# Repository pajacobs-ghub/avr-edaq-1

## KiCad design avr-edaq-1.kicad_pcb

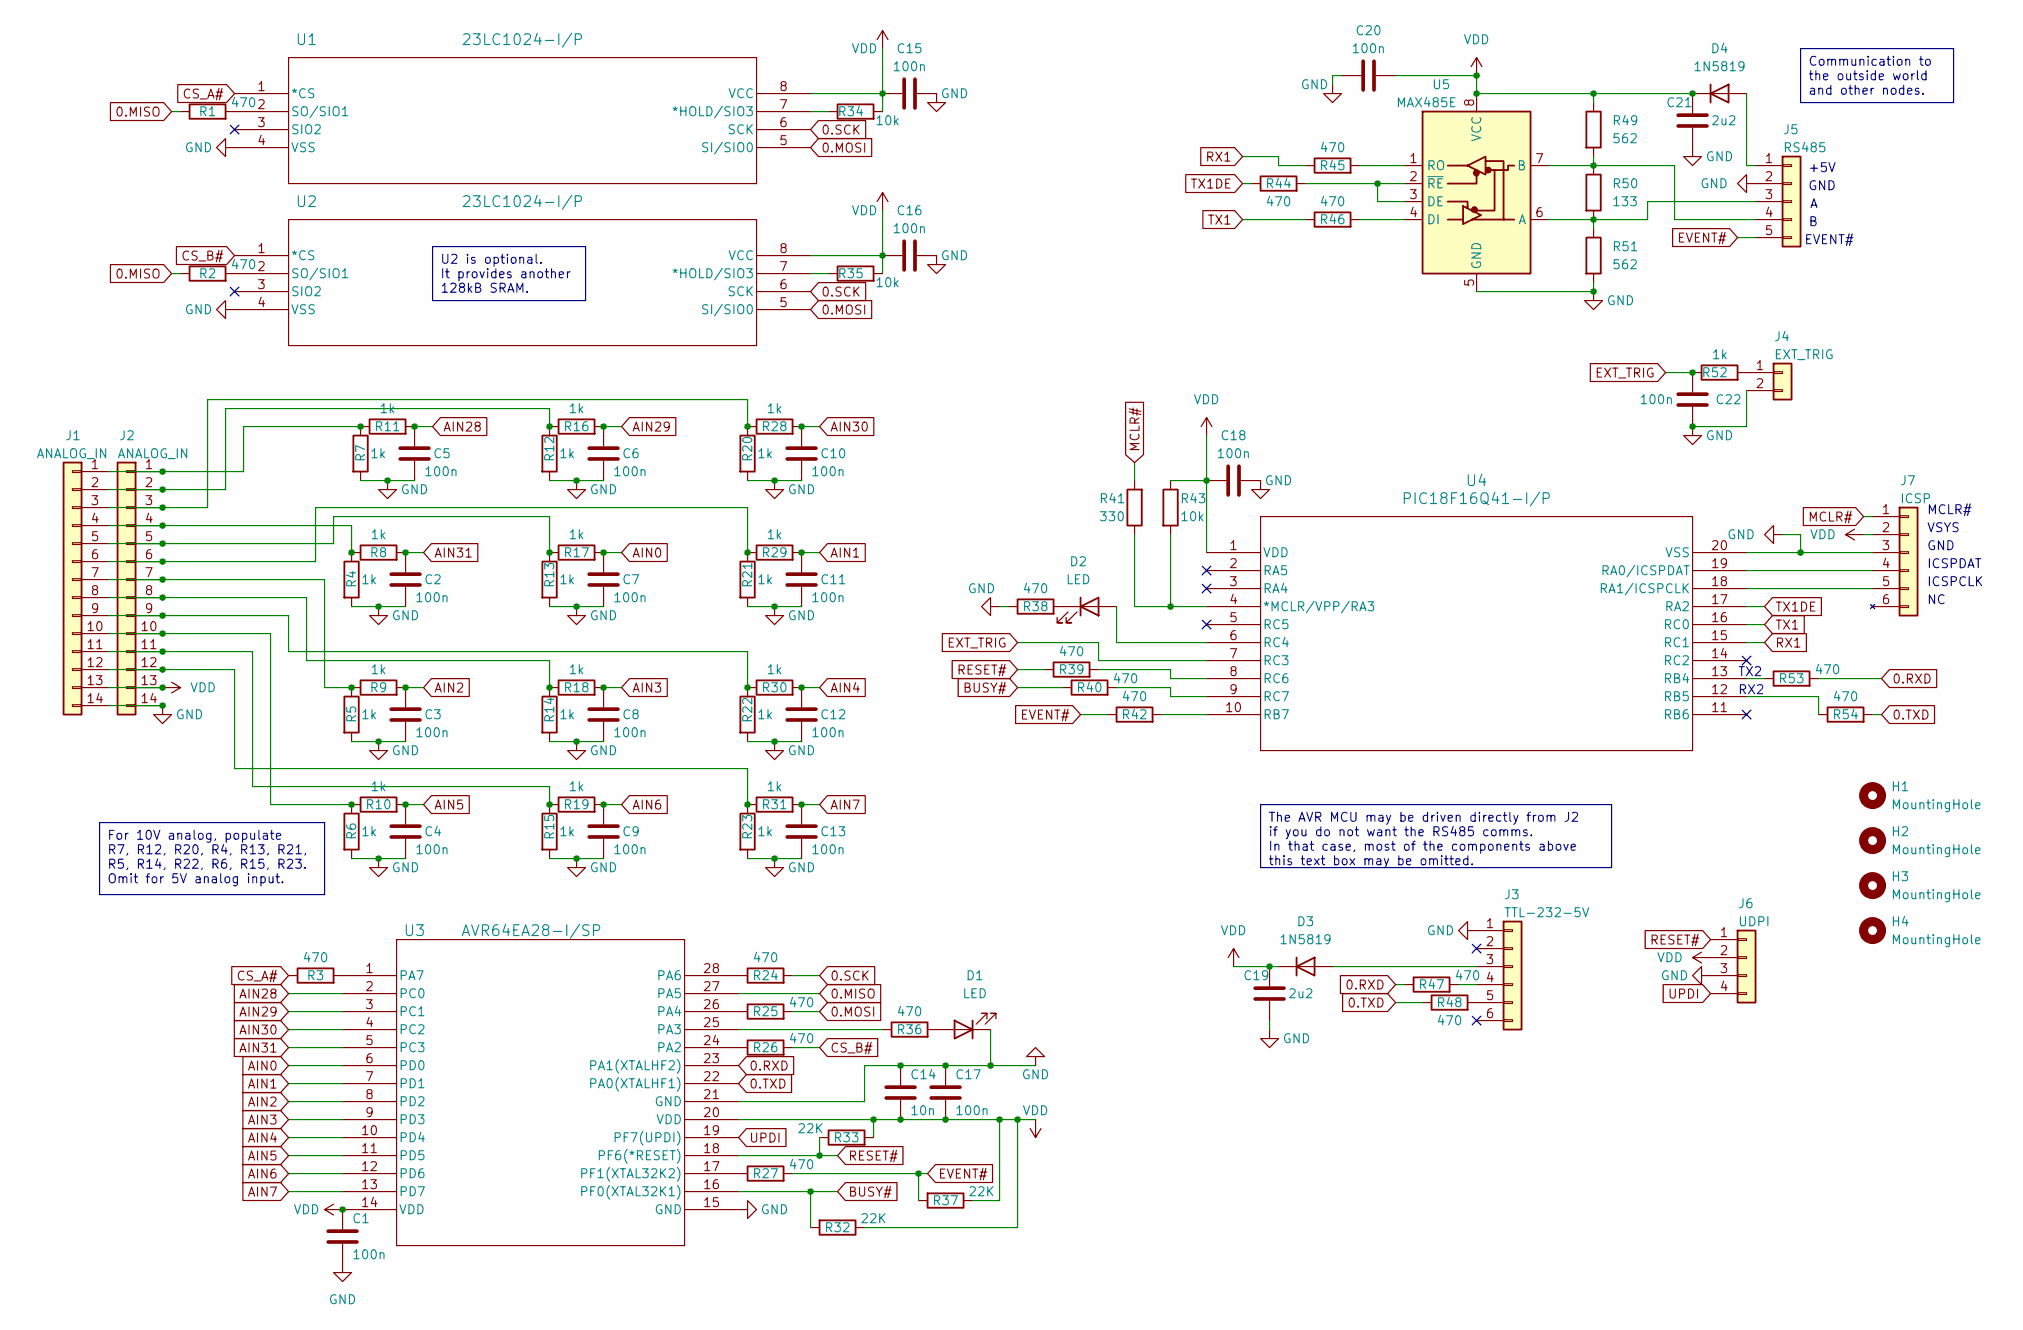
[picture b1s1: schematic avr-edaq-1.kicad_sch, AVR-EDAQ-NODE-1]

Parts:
C1, C2, C3, C4, C5, C6, C7, C8, C9, C10, C11, C12, C13, C15, C16, C17, C18, C20, C22: 100n; C_Disc_D4.7mm_W2.5mm_P5.00mm
C14: 10n; C_Disc_D4.7mm_W2.5mm_P5.00mm
C19, C21: 2u2; C_Disc_D4.7mm_W2.5mm_P5.00mm
D1, D2: LED; LED_D3.0mm
D3, D4: 1N5819; D_DO-41_SOD81_P10.16mm_Horizontal
H1, H2, H3, H4: MountingHole; MountingHole_3.2mm_M3
J1, J2: ANALOG_IN; PinHeader_1x14_P2.54mm_Vertical
J3: TTL-232-5V; PinHeader_1x06_P2.54mm_Vertical
J4: EXT_TRIG; PinHeader_1x02_P2.54mm_Vertical
J5: RS485; PinHeader_1x05_P2.54mm_Vertical
J6: UDPI; PinHeader_1x04_P2.54mm_Vertical
J7: ICSP; PinHeader_1x06_P2.54mm_Vertical
R1, R2, R3, R24, R25, R26, R27, R36, R38, R39, R40, R42, R44, R45, R46, R47, R48, R53, R54: 470; R_Axial_DIN0207_L6.3mm_D2.5mm_P10.16mm_Horizontal
R4, R5, R6, R7, R8, R9, R10, R11, R12, R13, R14, R15, R16, R17, R18, R19, R20, R21, R22, R23, R28, R29, R30, R31, R52: 1k; R_Axial_DIN0207_L6.3mm_D2.5mm_P10.16mm_Horizontal
R32, R33, R37: 22K; R_Axial_DIN0207_L6.3mm_D2.5mm_P10.16mm_Horizontal
R34, R35, R43: 10k; R_Axial_DIN0207_L6.3mm_D2.5mm_P10.16mm_Horizontal
R41: 330; R_Axial_DIN0207_L6.3mm_D2.5mm_P10.16mm_Horizontal
R49, R51: 562; R_Axial_DIN0207_L6.3mm_D2.5mm_P10.16mm_Horizontal
R50: 133; R_Axial_DIN0207_L6.3mm_D2.5mm_P10.16mm_Horizontal
U1, U2: 23LC1024-I/P; DIP-8_W7.62mm
U3: AVR64EA28-I/SP; DIP-28_W7.62mm
U4: PIC18F16Q41-I/P; DIP-20_W7.62mm
U5: MAX485E; DIP-8_W7.62mm

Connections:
0.MISO: R1.1, R2.1, U3.27 (PA5)
0.MOSI: R25.2, U1.5 (SI/SIO0), U2.5 (SI/SIO0)
0.RXD: R47.1, R53.2, U3.23 (PA1(XTALHF2))
0.SCK: R24.2, U1.6 (SCK), U2.6 (SCK)
0.TXD: R48.1, R54.2, U3.22 (PA0(XTALHF1))
AIN0: C7.1, R17.2, U3.6 (PD0)
AIN1: C11.1, R29.2, U3.7 (PD1)
AIN2: C3.1, R9.2, U3.8 (PD2)
AIN3: C8.1, R18.2, U3.9 (PD3)
AIN4: C12.1, R30.2, U3.10 (PD4)
AIN5: C4.1, R10.2, U3.11 (PD5)
AIN6: C9.1, R19.2, U3.12 (PD6)
AIN7: C13.1, R31.2, U3.13 (PD7)
AIN28: C5.1, R11.2, U3.2 (PC0)
AIN29: C6.1, R16.2, U3.3 (PC1)
AIN30: C10.1, R28.2, U3.4 (PC2)
AIN31: C2.1, R8.2, U3.5 (PC3)
BUSY#: R32.2, R40.1, U3.16 (PF0(XTAL32K1))
CS_A#: R3.1, U1.1 (*CS)
CS_B#: R26.2, U2.1 (*CS)
EVENT#: J5.5, R27.2, R37.2, R42.1
EXT_TRIG: C22.1, R52.1, U4.7 (RC3)
GND: C1.2, C2.2, C3.2, C4.2, C5.2, C6.2, C7.2, C8.2, C9.2, C10.2, C11.2, C12.2, C13.2, C14.1, C15.2, C16.2, C17.1, C18.2, C19.2, C20.1, C21.2, C22.2, D1.1 (K), J1.14, J2.14, J3.1, J4.2, J5.2, J6.3, J7.3, R4.2, R5.2, R6.2, R7.2, R12.2, R13.2, R14.2, R15.2, R20.2, R21.2, R22.2, R23.2, R38.1, R51.2, U1.4 (VSS), U2.4 (VSS), U3.15 (GND), U3.21 (GND), U4.20 (VSS), U5.5 (GND)
MCLR#: J7.1, R41.2
unnamed: D1.2 (A), R36.2
unnamed: D2.2 (A), U4.6 (RC4)
unnamed: D2.1 (K), R38.2
unnamed: D3.2 (A), J3.3
unnamed: D4.2 (A), J5.1
unnamed: J1.1, J2.1, R7.1, R11.1
unnamed: J1.2, J2.2, R12.1, R16.1
unnamed: J1.3, J2.3, R20.1, R28.1
unnamed: J1.4, J2.4, R4.1, R8.1
unnamed: J1.5, J2.5, R13.1, R17.1
unnamed: J1.6, J2.6, R21.1, R29.1
unnamed: J1.7, J2.7, R5.1, R9.1
unnamed: J1.8, J2.8, R14.1, R18.1
unnamed: J1.9, J2.9, R22.1, R30.1
unnamed: J1.10, J2.10, R6.1, R10.1
unnamed: J1.11, J2.11, R15.1, R19.1
unnamed: J1.12, J2.12, R23.1, R31.1
unnamed: J3.4, R47.2
unnamed: J3.5, R48.2
unnamed: J4.1, R52.2
unnamed: J5.3, R50.2, R51.1, U5.6 (A)
unnamed: J5.4, R49.2, R50.1, U5.7 (B)
unnamed: J7.4, U4.19 (RA0/ICSPDAT)
unnamed: J7.5, U4.18 (RA1/ICSPCLK)
unnamed: R34.1, U1.7 (*HOLD/SIO3)
unnamed: R1.2, U1.2 (SO/SIO1)
unnamed: R35.1, U2.7 (*HOLD/SIO3)
unnamed: R2.2, U2.2 (SO/SIO1)
unnamed: R26.1, U3.24 (PA2)
unnamed: R36.1, U3.25 (PA3)
unnamed: R25.1, U3.26 (PA4)
unnamed: R24.1, U3.28 (PA6)
unnamed: R3.2, U3.1 (PA7)
unnamed: R27.1, U3.17 (PF1(XTAL32K2))
unnamed: R41.1, R43.2, U4.4 (*MCLR/VPP/RA3)
unnamed: R53.1, U4.13 (RB4)
unnamed: R54.1, U4.12 (RB5)
unnamed: R42.2, U4.10 (RB7)
unnamed: R39.2, U4.8 (RC6)
unnamed: R40.2, U4.9 (RC7)
unnamed: R44.2, U5.2 (~RE), U5.3 (DE)
unnamed: R46.2, U5.4 (DI)
unnamed: R45.2, U5.1 (RO)
RESET#: J6.1, R33.1, R39.1, U3.18 (PF6(*RESET))
RX1: R45.1, U4.15 (RC1)
TX1: R46.1, U4.16 (RC0)
TX1DE: R44.1, U4.17 (RA2)
UPDI: J6.4, U3.19 (PF7(UPDI))
VDD: C1.1, C14.2, C15.1, C16.1, C17.2, C18.1, C19.1, C20.2, C21.1, D3.1 (K), D4.1 (K), J1.13, J2.13, J6.2, J7.2, R32.1, R33.2, R34.2, R35.2, R37.1, R43.1, R49.1, U1.8 (VCC), U2.8 (VCC), U3.14 (VDD), U3.20 (VDD), U4.1 (VDD), U5.8 (VCC)

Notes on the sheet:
The AVR MCU may be driven directly from J2 if you do not want the RS485 comms. In that case, most of the components above this text box may be omitted.
U2 is optional. It provides another 128kB SRAM.
Communication to the outside world and other nodes.
For 10V analog, populate R7, R12, R20, R4, R13, R21, R5, R14, R22, R6, R15, R23. Omit for 5V analog input.
MCLR#
ICSPDAT
VSYS
+5V
RX2
TX2
GND
ICSPCLK
EVENT#

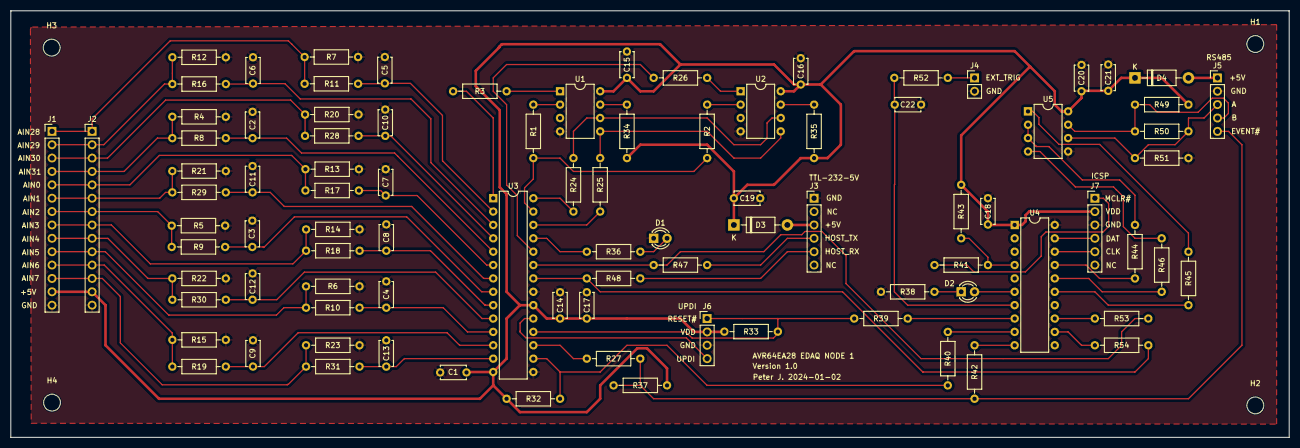
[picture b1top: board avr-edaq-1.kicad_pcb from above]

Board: 2 copper layers, 242.9 x 81.0 mm, 96 parts (0 on the bottom side), 73 nets.

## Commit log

2024-09-24 KiCAD files as sent for fabrication 2024-01-02
